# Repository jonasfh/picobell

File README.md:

# PicoBell Doorbell Project

Prosjekt for å gjøre eksisterende porttelefon smartere.   Målet er å kunne motta ringesignaler på mobil, og åpne døren fra en egen app – uten å miste dagens funksjonalitet.

Se [docs](docs/) for detaljert dokumentasjon.

## Struktur

    doorbell-project/
    │
    ├── pico/                # Alt for Pico-mikrokontrolleren
    │   ├── firmware/        # C++/Micropython/Pico SDK kode
    │   └── docs/            # Notater om HW-tilkobling, skjema osv.
    │
    ├── server/           # PHP-backend (API)
    │   ├── public/       # Web-root (index.php)
    │   ├── src/          # PHP-kode (controllers, services)
    │   ├── config/       # Konfig (dotenv, secrets, firebase.json)
    │   ├── vendor/       # Composer dependencies
    │   ├── composer.json # Composer config
    │   └── composer.lock
    │
    ├── mobile/              # Klient-app
    │   ├── android/         # Android-kode
    │   ├── ios/             # (ev. senere)
    │   └── shared/          # Felles ressurser (ikon, assets, logoer)
    │
    ├── docs/                # Arkitekturdiagrammer, flyt, API-spec
    │
    └── .gitignore

## Systemoversikt

```mermaid
flowchart LR
    subgraph Mobile["Android app"]
        M1["Bruker logger inn med Google"]
        M2["Får JWT fra server"]
        M3["Kaller /profile-endepunkter"]
    end

    subgraph Web["Web (test/cli)"]
        W1["Kan kalle auth/google"]
        W2["Kan teste med JWT"]
    end

    subgraph Server["Picobell server (Slim/PHP)"]
        S1["AuthController"]
        S2["ProfileController"]
        S3["DevicesController"]
        S4["ApartmentsController"]
        S5["AdminController"]
    end

    subgraph DB["SQLite (dev) / Postgres (prod senere?)"]
        D1["users"]
        D2["devices"]
        D3["apartments"]
        D4["user_apartment (role)"]
    end

    M1 --> S1
    W1 --> S1
    S1 --> D1
    S1 --> M2
    S1 --> W2
    M3 --> S2
    M3 --> S3
    M3 --> S4
    S2 --> D1
    S3 --> D2
    S4 --> D3
    S4 --> D4
    S5 --> D1
    S5 --> D2
    S5 --> D3
```

## Arkitektur (oversikt)

```mermaid
flowchart LR
    subgraph HW[Raspberry Pi Pico + Porttelefon]
        BELL[Ringesignal deteksjon] --> PICO
        BTN["Døråpner-knapp (relé)"] --> PICO
        PICO -- "MikroPython/C++" --> WIFI((WiFi))
    end

    WIFI --> SERVER[Python backend på NREC]

    subgraph SERVER
        API["REST API (FastAPI/Flask)"]
        QUEUE["Message Queue (opsjon)"]
        FCM[Firebase Cloud Messaging]
    end

    SERVER <--> API
    API --> FCM

    FCM --> APP[Android/iOS App]
    APP <--> API
```

## Komponenter

* Pico: Leser ringesignalet, styrer døråpner.
* Server: Python (FastAPI/Flask). Håndterer API, push-varsler, autentisering.
* Mobilapp: Android (og evt. iOS). Mottar varsler, gir bruker mulighet til å åpne dør.

## Database

Det er behov for en database for følgende oppgaver:

* Registrering av brukere
* Registrering av leiligheter/picoer

```mermaid
erDiagram
    USERS {
        int      id
        string   email
        string   password_hash
        string   display_name
        string   phone
        datetime created_at
        datetime updated_at
    }

    APARTMENTS {
        int      id
        string   name
        string   address
        string   pico_id
        string   fw_version
        string   metadata
        datetime created_at
    }

    USER_APARTMENT {
        int      id
        int      user_id
        int      apartment_id
        string   role
        datetime created_at
    }

    DEVICE_TOKENS {
        int      id
        int      user_id
        string   token
        string   platform
        datetime created_at
        datetime last_seen
    }

    AUDIT_LOG {
        int      id
        int      user_id
        string   event_type
        string   details
        string   ip
        datetime created_at
    }

    USERS ||--o{ USER_APARTMENT : has
    APARTMENTS ||--o{ USER_APARTMENT : has
    USERS ||--o{ DEVICE_TOKENS : owns
    USERS ||--o{ AUDIT_LOG : generates
```

## Sikkerhet

* Pico fungerer kun som klient, aldri åpen port mot internett.
* Server kjører med TLS (nginx som reverse proxy).
* Push-varsler håndteres via Firebase (Android) og evt. APNs (iOS).
* API autentisering med tokens (JWT eller lignende).

## Authentisering

```mermaid
sequenceDiagram
    participant U as User (Android/Web)
    participant G as Google OAuth
    participant S as Picobell Server
    participant DB as Database

    U->>G: Login with Google
    G-->>U: Google ID token
    U->>S: POST /auth/google (ID token)
    S->>G: Verify ID token
    G-->>S: Token valid + user info
    S->>DB: Lookup user by email
    DB-->>S: User found or new created
    S-->>U: JWT (id, email, role)

    U->>S: Call protected endpoint (with Bearer JWT)
    S->>S: Verify JWT signature
    S->>DB: (optional) fetch user details
    DB-->>S: User info
    S-->>U: Response
```

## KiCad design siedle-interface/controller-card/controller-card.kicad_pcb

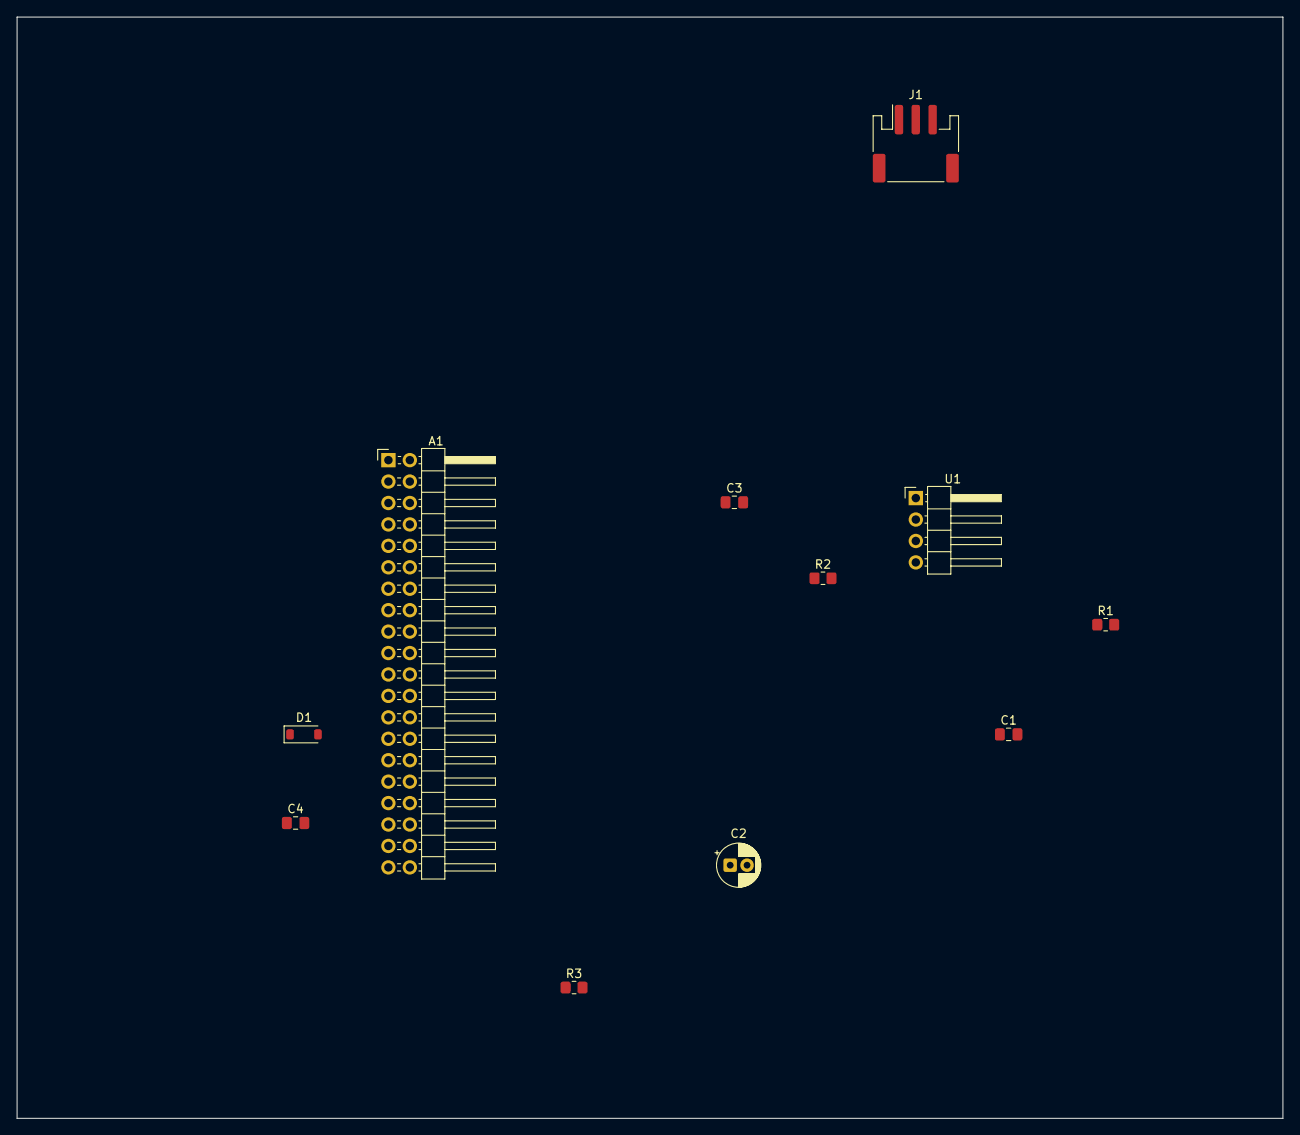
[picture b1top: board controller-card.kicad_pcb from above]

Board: 2 copper layers, 150.0 x 130.5 mm, 11 parts (0 on the bottom side), 7 nets, no tracks yet.

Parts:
A1: RaspberryPi_Pico_W; PinHeader_2x20_P2.54mm_Horizontal
C1, C3, C4: 100nF; C_0805_2012Metric_Pad1.18x1.45mm_HandSolder
C2: 10uF; CP_Radial_D5.0mm_P2.00mm
D1: Schottky, clamp; D_SOD-123
J1: Conn_01x03; JST_PH_S3B-PH-SM4-TB_1x03-1MP_P2.00mm_Horizontal
R1: 100kOhm; R_0805_2012Metric_Pad1.20x1.40mm_HandSolder
R2: 10kOhm; R_0805_2012Metric_Pad1.20x1.40mm_HandSolder
R3: 10kOhm seriemotstand; R_0805_2012Metric_Pad1.20x1.40mm_HandSolder
U1: LM2596S MODULE; PinHeader_1x04_P2.54mm_Horizontal

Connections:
/+27.7V: J1.2, R1.1, U1.1 (VIN)
/GND: A1.3 (GND), A1.8 (GND), A1.13 (GND), A1.18 (GND), A1.23 (GND), A1.28 (GND), A1.38 (GND), C1.2, C2.1, C3.1, R2.2, U1.2 (OUT)
/Out+ 5V: A1.39 (VSYS), C2.2, C3.2, U1.4 (FB)
/Ring på - signal <3.3V: A1.31 (GPIO26_ADC0), D1.1 (K), R3.2
/Use 3V3 as ADC reference: A1.35 (ADC_VREF), A1.36 (3V3), C4.2, D1.2 (A)
unnamed: A1.33 (AGND), C4.1
unnamed: C1.1, R1.2, R2.1, R3.1

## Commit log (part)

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2025-09-14 Service for handling FCM messages with android via Google
2025-09-14 Support for notifications
2025-09-14 Install guzzle for Firebase FCM support
2025-09-14 Rename picobell -> picobelltaco
2025-09-14 Install google/auth
2025-09-14 Remove secret
2025-09-15 Fix syntax error in flowchart
2025-09-15 Forslag til oppsett av database
2025-09-15 Install medoo (API), phinx (db migration)
2025-09-15 Install db drivers
2025-09-15 Create base tables and seed with dummy data
2025-09-17 Clean up, rename keys
2025-09-17 Install sqlite
2025-09-17 Add devices table, and seeding for dev
2025-09-17 Default database setup
2025-09-17 Oppdatert readme og db-oppsett for utvikling
2025-09-17 Reinventing database setup
2025-09-17 Update routes to include CRUD functionality
2025-09-17 Use db 'namespace' for CRUD functionality
2025-09-17 Forgot to keep the doorbell - functionality
2025-09-17 Deploy-workflow
2025-09-17 Handle ssh keys better
2025-09-17 Use env inside the action
2025-09-17 Use correct environment
2025-09-17 Specify key to use
2025-09-17 Include username
2025-09-17 Remember to fetch first...
2025-09-18 Also run composer
2025-09-18 Env vars not parsed in heredoc
2025-09-18 Remember composer setup is in server-folder
2025-09-18 Use same config setup for dev and production
2025-09-18 Deploy to dev and prod
2025-09-18 Dont fail if env-file not found
2025-09-18 Fix deploy-script
2025-09-18 Only notice if .env not found
2025-09-18 deployfix
2025-09-18 Fix migration
2025-09-18 deployscript
2025-09-18 DatabaseSeeder ensure seed files run in correct order
2025-09-18 Deploy to ProISP and adapt to MySQL
    * Include username
    * Remember to fetch first...
    * Also run composer
    * Env vars not parsed in heredoc
    * Remember composer setup is in server-folder
    * Use same config setup for dev and production
2025-09-19 Dev deployments dont really work as intended
2025-09-19 Fix dev deployment issues
2025-09-21 Options All fails on proisp server host
2025-09-21 Block access to config files
2025-09-21 Do magic outside webroot, then copy to webroot
2025-09-21 Seed files need dependency checking to work properly
2025-09-21 Manual workflow to seed database with dummy data
2025-09-21 Always run. This wf is run manually
2025-09-22 Move composer install and db migration for faster install
2025-09-23 Utility scripts for database migration and seeding
2025-09-23 Install firebase jwt library
2025-09-23 Add user management and auth controller
2025-09-23 Remove username
2025-09-24 Add role column to users table
2025-09-25 Also remove username from seed (see a6d94bc)
2025-09-26 Forbedret routes, profile fungerer
2025-10-04 Update defaults
2025-10-04 Install google api client
2025-10-04 Google auth start
2025-10-05 Need the client id for the OAUTH google app
2025-10-05 Add middleware parser, fix medoo insert handling...
    - Also set password to optional in db
2025-10-05 Update docs
2025-10-06 User can only connect to single apartment
2025-10-06 Make sure device always has user
2025-10-06 (#7) register device endpoint
2025-10-06 Refactor routes
2025-10-06 Protect admin-endpoints
2025-10-06 Move devices and apartm. to profile/ endpoints
2025-10-06 Server endpoints
2025-10-06 Penere visning
2025-10-06 Docs update
2025-10-06 member is default role
2025-10-06 Upgrade android project
2025-10-06 Bibliotek for google Oauth2
2025-10-06 Test-bibliotek
2025-10-06 Authenticate to google and register device
2025-10-06 Add config for server url and OAUTH client
2025-10-06 Ignorer deprecated - meldinger
2025-10-07 Add Logs. Also use Web Oauth client id with firebase
2025-10-07 Update deployment with JWT seed and Google service account
2025-10-07 Chmod the correct path
2025-10-07 Add google client id. Also dont display secrets in logs
2025-10-07 Debugging-info
2025-10-07 Write to log instead
2025-10-07 Temp diplay of headers in prod
2025-10-07 Allow Auth headers for PHP
2025-10-07 Use http auth. Remove obsolete logs
2025-10-07 Add last_seen column to devices
2025-10-07 Update device if already exists
2025-10-07 Use the correct input
2025-10-07 Fix generation of service-account.json
2025-10-07 Doorbell ring sender melding til alle i leiligheten
2025-10-08 Explain Google Firebase cloud messaging API
2025-10-08 Install Retrofit http library
2025-10-08 Remove secrets from logs
2025-10-09 (#12) Pass apartment_id as data payload
2025-10-09 (#8) Add os column, default android
2025-10-09 Temporarily disable dev workflow
2025-10-10 Add doorbell_events and api_log tables
2025-10-10 New endpoint status
2025-10-10 Clarifying docs
2025-10-11 Logging middleware
2025-10-15 Ignore kotlin logs etc
2025-10-15 (#9) Show profile in app
2025-10-15 (#13) Token manager to handle jwt safely
2025-10-15 Refactoring: move to auth package and rename
2025-10-15 Create UI from profile data
2025-10-15 Use Auth-interceptor for OKHTTP3 http client
2025-10-15 TokenManager for handling jwt token
2025-10-15 Improve layout. Fix delete device button
2025-10-18 Fix the doorbell
2025-10-18 Fix subtle errors
2025-12-03 Debugging
2025-12-03 Funksjon for aktivering av Åpne knapp
    - Deaktiveres automatisk etter 120 sek
    - Inklurerer en test-knapp, som fjernes senere
2025-12-03 Doorbell fungerer gitt!
2025-12-04 (#21) Broadcast ring events to app, activate open apt button
2025-12-06 (#22) Pure data messages instead of notification
2025-12-06 Install the google cloud cli
2025-12-06 (#24) Make sure user is allowed to open the door
2025-12-06 (#21) Make sure button is active, and open door when clicked
2025-12-06 (#27) Open app when clicking notification
2025-12-06 (#29) First attempt at BLE service
2025-12-06 (#29) Save wifi setup to file
2025-12-07 (#36) Broadcast name correctly to BLE
2025-12-07 End provisioning after 5 minutes or of provision ready
2025-12-07 Documentation
2025-12-07 (#30) Remove 'button' feature
    - Add this later using physical Open - button on the door-phone
2025-12-07 (#30) Support for reboot by long pressing door open (GPIO 15)
2025-12-07 (#38) Send doorbell ring fra pico
2025-12-07 Fix some container issues
2025-12-07 (#34) Add api key to apartments table
2025-12-07 (#34) Update controller with api key
2025-12-07 (#34) Update apartment funct in controllers
2025-12-07 Filter output for logged in user
2025-12-07 Update to use device API key for auth
2025-12-08 (#41, #42) Add api key to ble, and show service names
2025-12-08 Docs-update, missing image
2025-12-08 Add menu to allow pico setup
2025-12-08 Read SSID from wifi setup
2025-12-08 BLE scanning works on my phone
2025-12-09 (#32) Fix permission issue
2025-12-09 (#32) UI for wifi setup in Picobell
2025-12-09 (#32) Setup wifi i Pico
2025-12-09 (#32) Add random device_api_key
2025-12-09 (#32) Nesten klar. Opprettelse av leilighet feiler pga auth
2025-12-09 (#32) Provisioning works!
2025-12-10 Create CONNECTIONS.md for doorphone wiring diagram
    Added a connection diagram for the doorphone and Pico setup.
2025-12-10 (#46) Auto add created apartment to user
2025-12-10 (#49) Allow owner to rename apartment
2025-12-10 (49) Allow owner to delete apartment
2025-12-10 (#51) Fix issues with open - call
2025-12-10 (#53) Use api_key from server
    - Also repository functions for update and delete apartment
2025-12-10 Add new env variable
2025-12-10 Move Open door logic to ApartmentRepository
2025-12-10 Display friendly user message
2025-12-10 (#53) Delete apartment
2025-12-11 (#53) UI to rename apartment
2025-12-11 (#53) Notify if delete fails
2025-12-12 Remove sensitive debug info
2025-12-12 Workflow to publish policies to github pages
    GitHub Actions workflow for deploying policies and other info to github pages.
2025-12-12 (#58) Add policies
2025-12-12 (#58) Terms of service + support pages
2025-12-12 Rename to static.yml
2025-12-12 Render markdown as HTML
2025-12-12 (#58) Index page
2025-12-12 Dont hard code value, set as varable in github instead
2025-12-12 Expose user role on apartment
2025-12-12 (#49) Only allow owner to se edit-button
2025-12-12 (#67) Only deploy if server folder changed
2025-12-12 (#66) Deploy android to github
2025-12-12 (#66) Fail if no changes to android folder
2025-12-12 (#66) Make sure only runs if needed
2025-12-12 Fix typos
2025-12-13 Always deploy. Hard to check changes since last deploy
2025-12-13 Use correct folder in monorepo
2025-12-13 Remove java home path
2025-12-13 Fix google services file and output
2025-12-13 Added changelog. Force update to changelog on release
2025-12-13 Search for changelog in correct folder
2025-12-14 Sign apk to make it installable
2025-12-14 Align apk file
2025-12-14 Forgot that workflow can filter on paths
2025-12-18 Bump version to build with new OAUTH client enabled
2025-12-18 Update changelog
2025-12-18 (#52) Check if Open was clicked in app, and open the door
2025-12-19 Remove message queue option from README diagram
    Removed the message queue option from the diagram.
2025-12-20 (#83) Versioning pico firmware
2025-12-20 chore(picofw): sync firmware version 0.0.1
2025-12-21 (#85) Led blink status communication
2025-12-21 chore(picofw): sync firmware version 0.0.2
2025-12-26 Fix error in diagram
2025-12-26 (#88) First try at schematic of controller card
2025-12-27 complete schematics
2026-01-04 Refactoring. New dev setup
2026-01-04 Pico version endpoint
2026-01-04 Update config from wifi settings, and simplify http calls
2026-01-04 Make sure file is closed after reading
    - Also secure mocking in hal.py
2026-01-04 API endpoints to upgrade pico firmware
2026-01-05 Safer config loader
2026-01-05 Protect .py files from beeing accessed or executed
2026-01-05 Test and docs for firmware upgrader
2026-01-05 Update docs, use ngrok for local api test from pico
2026-01-05 chore(picofw): sync firmware version 0.0.3
2026-01-05 Copy firmware files correctly
2026-01-06 No need. server/** will change with new pico version
2026-01-06 Refactor ble_provisioning to use hal.py + ble-tests
2026-01-06 chore(picofw): sync firmware version 0.0.4
2026-01-08 Run BLE config on Door open > 10s
    - Also update docs and some improvements
2026-01-08 Dev improvements: Idempotent seeding. composer dbinit for start
2026-01-09 chore(picofw): sync firmware version 0.0.5
2026-01-09 Usage instructions for mpremote
2026-01-09 Hello world e-ink screen
2026-01-09 Rotate the display
2026-01-09 Rotation support, also fast screen update
2026-01-10 Return a unix timestamp for pico
2026-01-10 Display info on screen
2026-01-10 Return local time from server
2026-01-10 chore(picofw): sync firmware version 0.0.6
2026-01-10 Display last call?
2026-01-10 Fix issue with large pico api key
    - BLE setup failed, only including the last part of the key
2026-01-10 chore(picofw): sync firmware version 0.0.7
2026-01-10 Remove test-code
2026-01-10 Show software update on screen
2026-01-10 chore(picofw): sync firmware version 0.0.8
2026-01-10 Emulate physical 200x200px screen for testing
2026-01-10 Rotate output 180deg on screen emulator
2026-01-10 chore(picofw): sync firmware version 0.0.9
2026-01-10 Display not showing OTA upgrade
2026-01-10 chore(picofw): sync firmware version 0.0.10
2026-01-10 Make sure pico runs even w/o display
2026-01-11 Make sure pico deploy always has changelog
2026-01-11 chore(picofw): sync firmware version 0.0.11
2026-01-12 (#100) Register analog Ring - event
2026-01-12 (#101) Power saving. Disable wifi and sleep
2026-01-13 Improve debug output
